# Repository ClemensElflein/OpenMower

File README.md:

<p align="center">
  <a>
    <h1 align="center">OpenMower - The DIY Smart Mowing Robot for Everyone</h1>
    
  </a>
</p>
<br>
<p align="center">
  
</p>
<br>
<p align="center"><b>Join the Discord server for OpenMower discussion:</b></p>
<p align="center"></p>
<br>
<br>

> [!WARNING]
> <p align="center"><b>DISCLAIMER:</b></p>
>
> **IF YOU ARE NOT 100% SURE WHAT YOU ARE DOING, PLEASE DON'T TRY THIS AT HOME! ASK IN [DISCORD](https://discord.gg/jE7QNaSxW7), IF YOU HAVE ANY QUESTIONS!**

> [!IMPORTANT]
> ### New users: start here → [openmower.de](https://openmower.de)
>
> This repository is the central entry point for the OpenMower project. The actual code, firmware and hardware designs live in dedicated repositories — see the [Ecosystem](#ecosystem) section below.

<br>

# About the Project

If you want to see a quick overview, check out this video:

<p align="center">
  
</p>

Let's be honest: The current generation of robotic lawn mowers sucks. Basically all of these bots drive in a random direction until they hit the border of the lawn, rotate for a randomized duration and repeat. **We can do better.**

OpenMower started by disassembling the cheapest off-the-shelf robotic mower we could find (YardForce Classic 500) and replacing its brain with custom hardware and open-source software — turning a dumb random-walk robot into a GPS-guided, map-aware, app-controlled mowing machine.

## Project Goals

:heavy_check_mark: **Autonomous Lawn Mowing:** The device mows the lawn automatically.

:heavy_check_mark: **Good Safety:** Emergency stop if lifted or crashed.

:heavy_check_mark: **No Perimeter Wire Needed:** Flexible support for multiple mowing areas.

:heavy_check_mark: **Low Cost:** Cheaper than a mid-range off-the-shelf product.

:heavy_check_mark: **Open:** Share knowledge and enable others to build their own OpenMower.

:heavy_check_mark: **Nice to Look At:** You should not be ashamed to have an OpenMower mowing your lawn.

:heavy_check_mark: **Avoid Obstacles:** Detect and avoid obstacles during mowing.

:heavy_check_mark: **Rain Detection:** Detect bad weather and pause until conditions improve.

<br>

# Open Mower App

<br>

# Getting Started

**Full documentation and step-by-step build guide:** [openmower.de](https://openmower.de)

The docs cover everything: compatibility checks, hardware shopping list (~€700 excl. mower and RTK base station), robot modification, software setup, and recording your mowing areas.

Before buying anything, read the [System Architecture overview](https://openmower.de/latest/docs/system-architecture/) and the [Step by Step Guide](https://openmower.de/latest/docs/step-by-step-guide/). The build requires intermediate electronics, Linux, and mechanical skills and typically takes a weekend for a YardForce-class mower.

**Need help?** Join the [Discord](https://discord.gg/jE7QNaSxW7) — 2000+ members, active community.

<br>

# Ecosystem

OpenMower is split across purpose-specific repositories, included here as submodules. Clone everything at once:

```bash
git clone --recursive https://github.com/ClemensElflein/OpenMower
```

Or fetch submodules after an existing clone:

```bash
git submodule update --init --recursive
```

## Software

| Repository | Local path | Description |
|---|---|---|
| [ClemensElflein/open_mower_ros](https://github.com/ClemensElflein/open_mower_ros) | `software/open_mower_ros` | ROS navigation, planning and state machine |
| [xtech/openmower-app](https://github.com/xtech/openmower-app) | `software/openmower-app` | Mobile and web app |
| [ClemensElflein/OpenMowerOS](https://github.com/ClemensElflein/OpenMowerOS) | `software/OpenMowerOS` | Operating system image |

## Firmware

| Repository | Local path | Description |
|---|---|---|
| [xtech/fw-openmower-v2](https://github.com/xtech/fw-openmower-v2) | `firmware/fw-openmower-v2` | Mainboard firmware — motor control, sensors, hardware abstraction |
| [ClemensElflein/xesc_firmware](https://github.com/ClemensElflein/xesc_firmware) | `firmware/xesc_firmware` | xESC motor controller firmware |

## Hardware

| Repository | Local path | Description |
|---|---|---|
| [xtech/hw-openmower-universal](https://github.com/xtech/hw-openmower-universal) | `hardware/hw-openmower-universal` | Universal mainboard |
| [xtech/hw-openmower-yardforce](https://github.com/xtech/hw-openmower-yardforce) | `hardware/hw-openmower-yardforce` | YardForce-specific mainboard |
| [xtech/hw-openmower-sabo](https://github.com/xtech/hw-openmower-sabo) | `hardware/hw-openmower-sabo` | Sabo / John Deere mainboard |

<br>

# Compatible Robotic Mowers

Many robotic mowers share the same underlying hardware manufactured by SUMEC Hardware, sold under brands like YardForce, Herkules, and others. By upgrading one of these robots, a large number of devices become OpenMower-capable.

Check the [openmower website](https://openmower.de/latest/docs/getting-started/#is-your-mower-compatible) to check, if your mower is compatible.

<br>

# How You Can Help

- **Build one** — validates the concept and generates useful documentation for others
- **Star ⭐ and watch 👀** this repository — helps with visibility
- **Contribute** — see [CONTRIBUTING.md](./CONTRIBUTING.md)
- **Support** — subscribe to the [YouTube channel](https://youtube.com/c/ClemensElflein)

<br>

# Patents, Local Laws, Liability

Before building a robot based on the designs published here, make sure you are allowed to do so in your specific region. There may be patents and/or laws prohibiting it.

The code/schematics/PCB files are distributed in the hope that they will be useful, but **WITHOUT ANY WARRANTY**; without even the implied warranty of MERCHANTABILITY or FITNESS FOR A PARTICULAR PURPOSE.

This is a documentation of a personal project, shared freely. I am not liable for any damages your devices cause to anyone or anything. You will need real technical know-how to use this project.

# License

**Licenses differ across the project.** Software repositories (ROS, app, OS, firmware) are generally licensed under GPL or MIT — check the `LICENSE` file in each individual repository before use.

This repository documentation is licensed under:

<br /><a rel="license" href="http://creativecommons.org/licenses/by-nc-sa/4.0/">Creative Commons Attribution-NonCommercial-ShareAlike 4.0 International</a>.

Feel free to use the design in private/educational projects. Don't sell the design or products based on it without consent. The goal is to share knowledge, not to enable others to sell this work.

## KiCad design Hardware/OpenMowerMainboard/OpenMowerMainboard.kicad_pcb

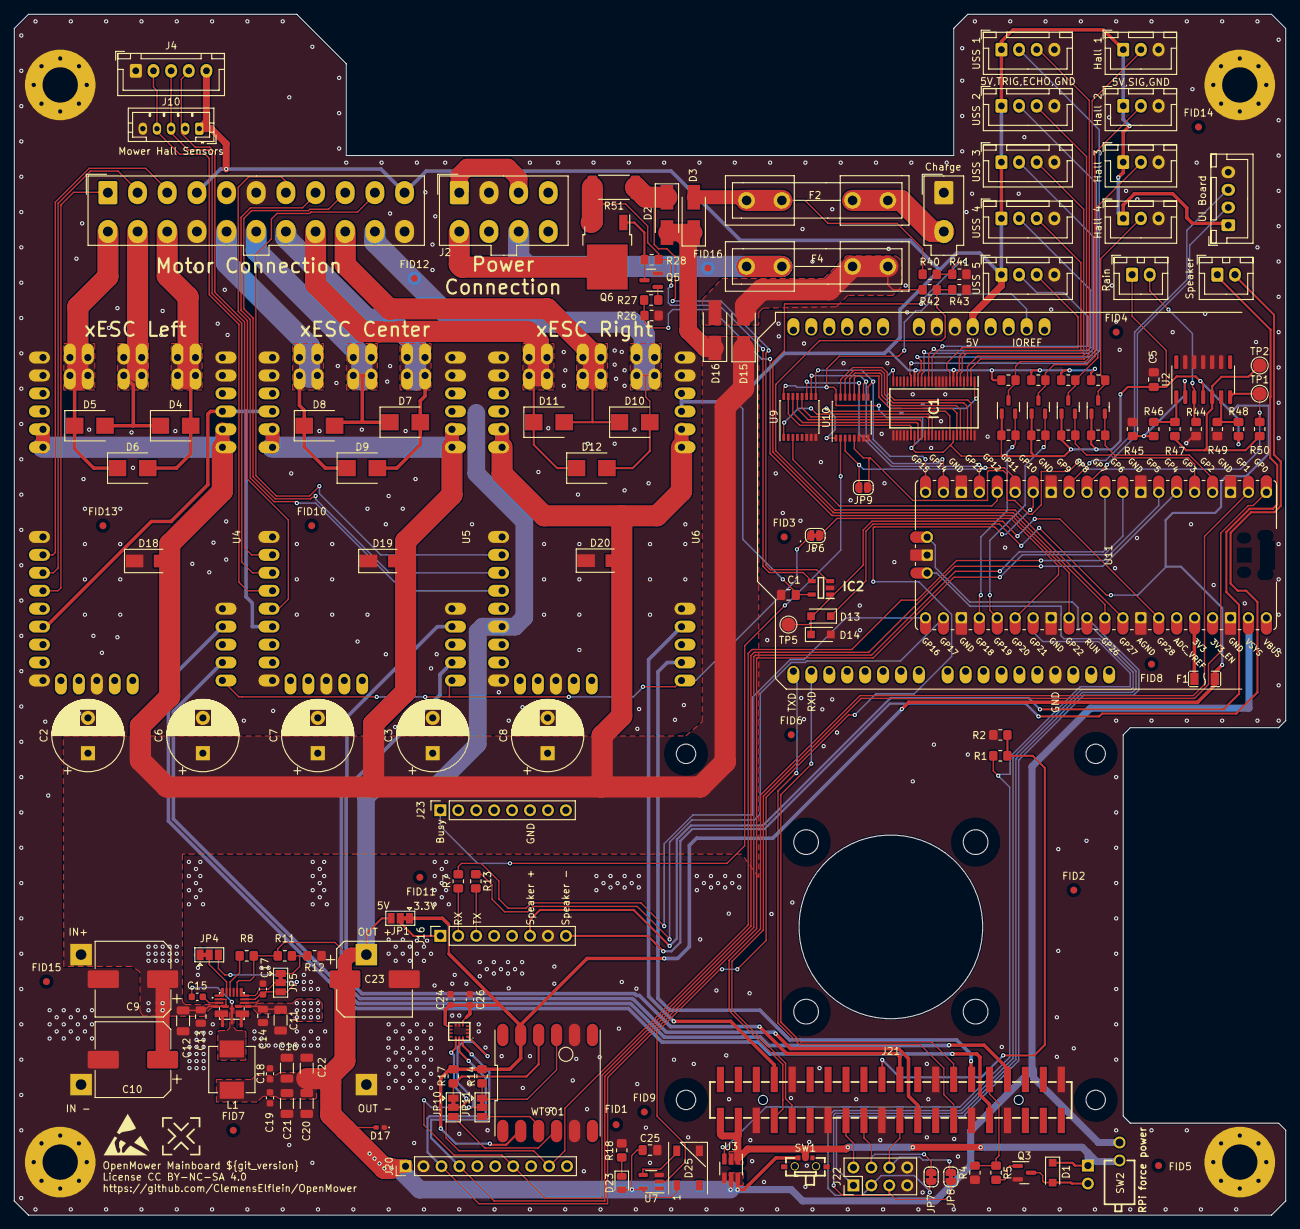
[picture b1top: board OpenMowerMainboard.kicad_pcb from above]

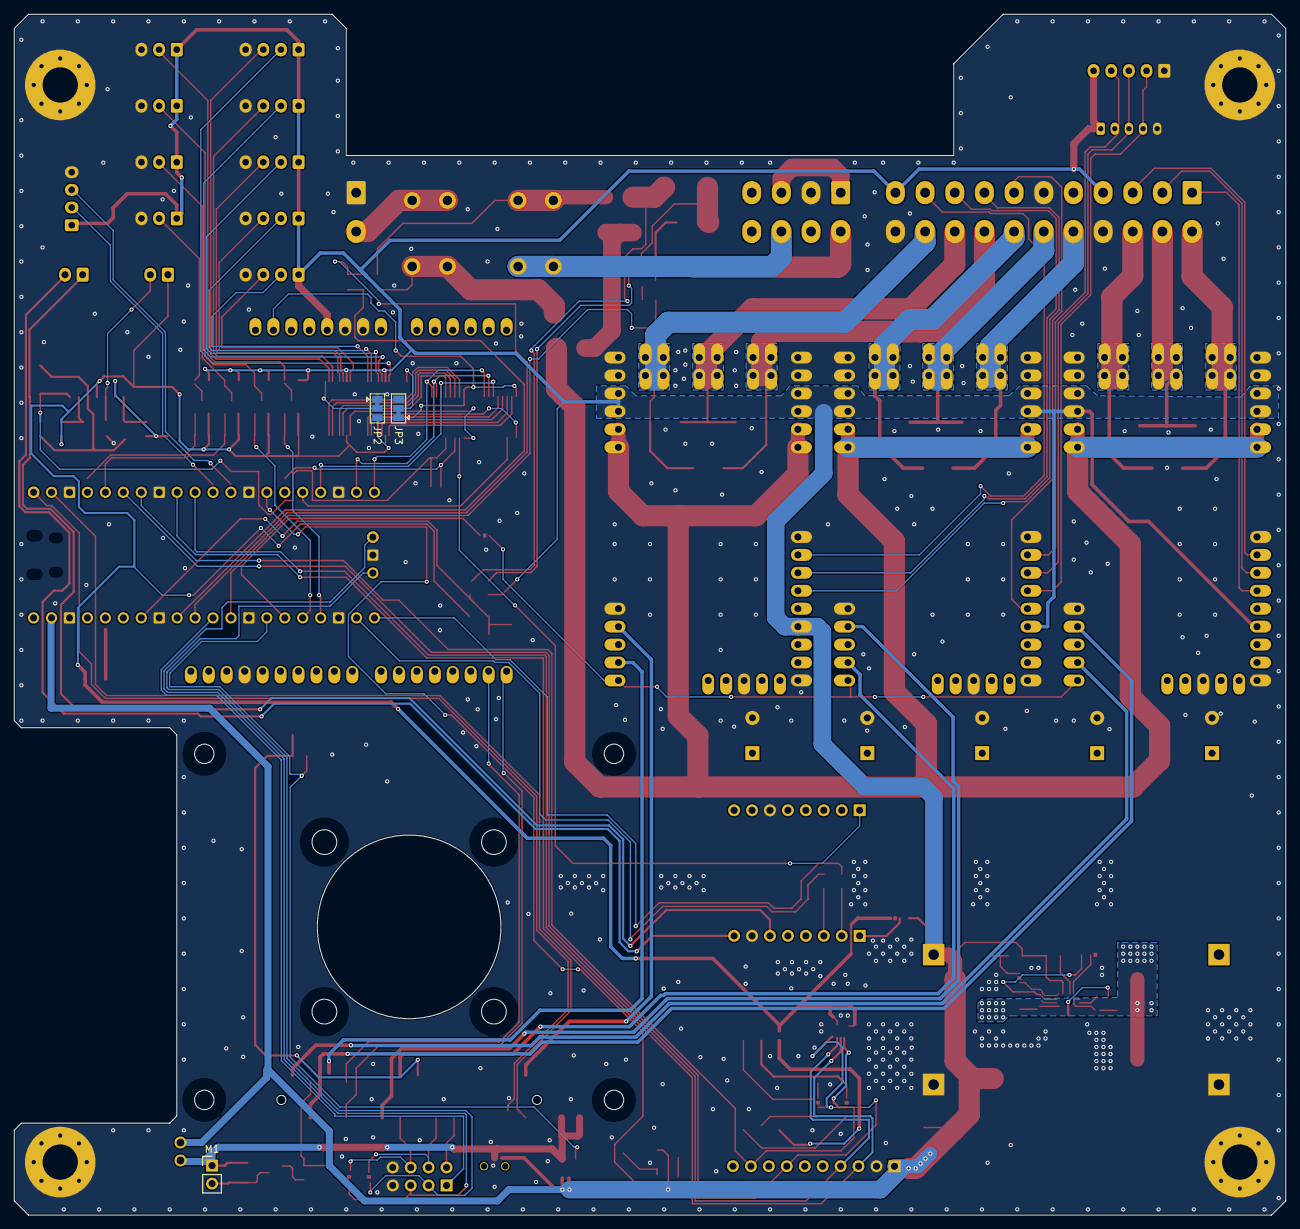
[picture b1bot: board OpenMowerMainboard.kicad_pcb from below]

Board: 2 copper layers, 180.0 x 170.0 mm, 178 parts (3 on the bottom side), 132 nets.

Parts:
AC1201: LSM6DSOTR; LGA-14_2.5X3X0.86_
C1, C5, C25: 100nF; C_0805_2012Metric_Pad1.18x1.45mm_HandSolder
C2, C3, C6, C7, C8: 220uF; CP_Radial_D10.0mm_P5.00mm
C9, C23: 680uF; CP_Elec_10x12.5
C10: DNP; CP_Elec_10x12.5
C11, C12: 4.7uF; C_1206_3216Metric
C13, C14: 1uF; C_0805_2012Metric
C15, C18, C19, C24, C26: 0.1uF; C_0603_1608Metric
C16, C20, C21, C22: 22uF; C_1206_3216Metric
C17: 2.2uF; C_0603_1608Metric
D1: D_Schottky; D_SOD-123F
D2, D3, D15, D16: D_Schottky; D_SMA_Handsoldering
D4, D5, D6, D7, D8, D9, D10, D11, D12: DNP; D_SMB
D13, D14: DNP; D_SOD-123F
D17: DNP; D_0402_1005Metric_Pad0.77x0.64mm_HandSolder
D18, D19, D20: DNP; D_SMA
D23: LED; LED_0805_2012Metric
D25: WS2812B; LED_WS2812B_PLCC4_5.0x5.0mm_P3.2mm
F1: nSMD035-16V; F1206
F2, F4: Fuse; Fuseholder5x20_horiz_open_inline_Type-I
FID1, FID2, FID3, FID4, FID5, FID6, FID7, FID8, FID9, FID10, FID11, FID12, FID13, FID14, FID15, FID16: Fiducial; Fiducial_1mm_Mask2mm
H1, H2, H3, H4: MountingHole_Pad; MountingHole_5mm_Pad_Via
IC1: 74ALVC164245DGG,11; SOP50P810X120-48N
IC2: TSC101CILT; SOT95P280X145-5N
IC3: MAX20405AFOF_VY+T; MAX2040
J1: Conn_02x11_Top_Bottom; Molex_Mini-Fit_Jr_5566-22A_2x11_P4.20mm_Vertical
J2: Conn_02x04_Top_Bottom; Molex_Mini-Fit_Jr_5566-08A_2x04_P4.20mm_Vertical
J3: Conn_01x02; Molex_Mini-Fit_Jr_5566-02A_2x01_P4.20mm_Vertical
J4: Conn_01x05; JST_XH_B5B-XH-A_1x05_P2.50mm_Vertical
J5, J6, J7, J8, J9, J19: Conn_01x04; JST_XH_B4B-XH-A_1x04_P2.50mm_Vertical
J10: Conn_01x05; JST_PH_B5B-PH-K_1x05_P2.00mm_Vertical
J11, J12, J13, J14: Conn_01x03_Male; JST_XH_B3B-XH-A_1x03_P2.50mm_Vertical
J16, J23: Conn_01x08; PinSocket_1x08_P2.54mm_Vertical
J17, J18: Conn_01x02; JST_XH_B2B-XH-A_1x02_P2.50mm_Vertical
J20: Conn_01x10_Female; PinHeader_1x10_P2.54mm_Vertical
J21: Raspberry_Pi_2_3; HDR-SMD_40P-P2.54-V-F-R2-C20-S8.8-EH
J22: Conn_02x04_Odd_Even; PinHeader_2x04_P2.54mm_Vertical
JP1, JP2, JP3, JP4, JP5: SolderJumper_3_Bridged12; SolderJumper-3_P1.3mm_Bridged12_Pad1.0x1.5mm
JP6, JP7, JP8: SolderJumper_2_Bridged; SolderJumper-2_P1.3mm_Bridged_RoundedPad1.0x1.5mm
JP9: SolderJumper_2_Open; SolderJumper-2_P1.3mm_Open_RoundedPad1.0x1.5mm
JP10, JP11: I2C_OR_TTL; SolderJumper-3_P1.3mm_Bridged12_Pad1.0x1.5mm
L1: 4.7uH 5A; L_Vishay_IHLP-2525
LOGO1: LOGO; ESD-Logo_6.6x6mm_SilkScreen
LOGO2: ESD-Logo_6.6x6mm_SilkScreen
M1: Fan; PinHeader_1x02_P2.54mm_Vertical
MH1, MH2, MH3, MH4, MH5, MH6, MH7, MH8: MountingHole_2.7mm_M2.5
Q3, Q5, Q13, Q14, Q15, Q16: BSS138; SOT-23
Q6: Q_PMOS_GDS; TO-252-2
R1, R2, R4, R12, R26, R28, R40, R42, R48, R50: 10k; R_0805_2012Metric_Pad1.20x1.40mm_HandSolder
R3, R6, R7, R9, R10, R13, R15, R16, R18, R19, R20, R41, R43, R45, R47: 1k; R_0805_2012Metric_Pad1.20x1.40mm_HandSolder
R5, R27: 150; R_0805_2012Metric_Pad1.20x1.40mm_HandSolder
R8: DNP; R_0805_2012Metric_Pad1.20x1.40mm_HandSolder
R11: 53k6 1%; R_0805_2012Metric_Pad1.20x1.40mm_HandSolder
R14, R17, R49: 4k7; R_0805_2012Metric_Pad1.20x1.40mm_HandSolder
R44, R46: 47k; R_0805_2012Metric_Pad1.20x1.40mm_HandSolder
R51: 0.003R; R_2512_6332Metric_Pad1.40x3.35mm_HandSolder
SW1: MK-11C04-G013; SW-SMD_MK-11C04-G013
SW2: DA-01BP; SW-TH_DA-01BP
TP1, TP2, TP5: TestPoint; TestPoint_Pad_D2.0mm
U1: DNP; LM2596S_MODULE
U2: MCP604; SOIC-14_3.9x8.7mm_P1.27mm
U3: SIP32509DT; SOT-23-6_Handsoldering
U4, U5, U6: xESC2
U7: SN74LV1T34DBV; SOT-23-5
U9, U10: 74HC4051; SSOP-16_4.4x5.2mm_P0.65mm
U11: Pico; Raspberry_Pi_Pico_SMT_THT
WT901: Conn_02x06_Female; WT901
XA1: Arduino_Uno_Shield

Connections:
+3V3: AC1201.5 (VDDIO), AC1201.8 (VDD), C5.2, C24.1, C26.1, D13.1 (K), F1.2, IC1.31 (VCC(A)_1), IC1.42 (VCC(A)_2), J17.1, JP1.1 (A), JP2.3 (B), JP3.1 (A), Q13.1 (G), Q14.1 (G), Q15.1 (G), Q16.1 (G), R3.1, R9.1, R14.2, R15.1, R17.2, R19.1, R48.2, U2.4 (V+), U9.16 (VCC), U10.16 (VCC), WT901.a2 (VCC), WT901.b2 (VCC), XA1.IORF (IOREF)
+5V: C1.1, C16.1, C18.1, C19.1, C20.1, C21.1, C22.1, C23.1, C25.1, D17.2 (A2), D23.2 (A), D25.1 (VDD), IC1.7 (VCC(B)_1), IC1.18 (VCC(B)_2), IC2.5 (VCC), IC3.13 (OUT), J1.4, J1.11, J4.5, J5.1, J6.1, J7.1, J8.1, J9.1, J10.1, J11.1, J12.1, J13.1, J14.1, J19.1, J20.1, JP1.3 (B), L1.2, R6.1, R8.2, R10.1, R11.2, R16.1, R20.1, SW1.1, SW2.2, U1.3 (OUT+), U3.5 (VIN), U3.6 (VIN), U4.5V, U5.5V, U6.5V, U7.5 (VCC), U11.39 (VSYS), XA1.5V1 (5V)
/CHARGE_CURRENT: D13.2 (A), D14.1 (K), IC2.1 (OUT), TP5.1, U11.34 (GPIO28_ADC2)
/ESCs/ESC_SHUTDOWN: JP6.1 (A), U11.26 (GPIO20)
/ESCs/MC_HALL_U: J4.2, J10.4, U5.4 (HALL_U)
/ESCs/MC_HALL_V: J4.3, J10.3, U5.5 (HALL_V)
/ESCs/MC_HALL_W: J4.4, J10.2, U5.6 (HALL_W)
/ESCs/MC_PHASE_U: D7.2 (A2), D9.2 (A2), J1.18, U5.U
/ESCs/MC_PHASE_V: D7.1 (A1), D8.2 (A2), J1.17, U5.V
/ESCs/MC_PHASE_W: D8.1 (A1), D9.1 (A1), J1.16, U5.W
/ESCs/MC_RX: J21.24 (~CE0/GPIO8), U5.14 (NCS/RX)
/ESCs/MC_TEMP: J1.7, U5.3 (TEMPERATURE)
/ESCs/MC_TX: J21.21 (MISO0/GPIO9), U5.12 (MOSI/TX)
/ESCs/ML_HALL_U: J1.1, U4.4 (HALL_U)
/ESCs/ML_HALL_V: J1.2, U4.5 (HALL_V)
/ESCs/ML_HALL_W: J1.3, U4.6 (HALL_W)
/ESCs/ML_PHASE_U: D4.2 (A2), D6.2 (A2), J1.14, U4.U
/ESCs/ML_PHASE_V: D4.1 (A1), D5.2 (A2), J1.13, U4.V
/ESCs/ML_PHASE_W: D5.1 (A1), D6.1 (A1), J1.12, U4.W
/ESCs/ML_RX: J21.32 (PWM0/GPIO12), U4.14 (NCS/RX)
/ESCs/ML_TX: J21.33 (PWM1/GPIO13), U4.12 (MOSI/TX)
/ESCs/MR_HALL_U: J1.8, U6.4 (HALL_U)
/ESCs/MR_HALL_V: J1.9, U6.5 (HALL_V)
/ESCs/MR_HALL_W: J1.10, U6.6 (HALL_W)
/ESCs/MR_PHASE_U: D10.2 (A2), D12.2 (A2), J1.21, U6.U
/ESCs/MR_PHASE_V: D10.1 (A1), D11.2 (A2), J1.20, U6.V
/ESCs/MR_PHASE_W: D11.1 (A1), D12.1 (A1), J1.19, U6.W
/ESCs/MR_RX: J21.7 (GCLK0/GPIO4), U6.14 (NCS/RX)
/ESCs/MR_TX: J21.29 (GCLK1/GPIO5), U6.12 (MOSI/TX)
/GPS/RXD: J21.27 (ID_SD/GPIO0), XA1.D1 (D1_TX0)
/GPS/TXD: J21.28 (ID_SC/GPIO1), XA1.D0 (D0_RX0)
/IMU/MISO: AC1201.1 (SDO/SA0), J20.7, JP11.2 (C), U11.6 (GPIO4)
/IMU/MOSI: AC1201.14 (SDA), J20.4, U11.10 (GPIO7)
/IMU/SCK: AC1201.13 (SCL), J20.3, U11.9 (GPIO6)
/IMU/~CS: AC1201.12 (CS), J20.9, JP10.2 (C), U11.7 (GPIO5)
/RAIN_DETECTED: JP9.1 (A), R50.2, TP1.1, U2.7, U10.5 (A5)
/RaspberryPi/PICO_RESET: J22.1, U11.30 (RUN)
/RaspberryPi/PICO_SWCLK: J22.5, JP8.1 (A), U11.41 (SWCLK)
/RaspberryPi/PICO_SWDIO: J22.3, JP7.1 (A), U11.43 (SWDIO)
/RaspberryPi/POWER_EN: R1.1, U3.3 (ENABLE), U11.27 (GPIO21)
/RaspberryPi/RASPI_FAN_ON: J21.31 (GCLK2/GPIO6), R4.2, R5.1
/RaspberryPi/RASPI_POWER: D1.1 (K), J21.2 (5V), J21.4 (5V), M1.1 (+), SW1.C, SW2.1, U3.1 (VOUT), U3.2 (VOUT)
/RaspberryPi/UART0_RXD: J21.10 (GPIO15/RXD), U11.1 (GPIO0)
/RaspberryPi/UART0_TXD: J21.8 (GPIO14/TXD), U11.2 (GPIO1)
/RobotConnectors/CHARGE_SHUNT_MINUS: IC2.4 (VM), Q6.3 (S), R28.1, R51.2
/RobotConnectors/CHARGE_SHUNT_PLUS: D2.1 (K), IC2.3 (VP), R51.1
/RobotConnectors/ENABLE_CHARGE: R26.1, R27.1, U11.29 (GPIO22)
/RobotConnectors/HALL_SWITCH_1: Q13.2 (S), R3.2, U11.24 (GPIO18)
/RobotConnectors/HALL_SWITCH_1_5V: J11.2, Q13.3 (D), R6.2
/RobotConnectors/HALL_SWITCH_2: Q14.2 (S), R9.2, U11.25 (GPIO19)
/RobotConnectors/HALL_SWITCH_2_5V: J12.2, Q14.3 (D), R10.2
/RobotConnectors/HALL_SWITCH_3: Q15.2 (S), R15.2, U11.5 (GPIO3)
/RobotConnectors/HALL_SWITCH_3_5V: J13.2, Q15.3 (D), R16.2
/RobotConnectors/HALL_SWITCH_4: Q16.2 (S), R19.2, U11.4 (GPIO2)
/RobotConnectors/HALL_SWITCH_4_5V: J14.2, Q16.3 (D), R20.2
/RobotConnectors/LED_RX: J19.2, U11.11 (GPIO8)
/RobotConnectors/LED_TX: J19.3, U11.12 (GPIO9)
/RobotConnectors/MosfetSwitch/VOUT: J2.5, Q6.2 (D)
/RobotConnectors/RAIN-: J17.2, R44.2, U2.3 (+)
/RobotConnectors/SPEAKER_MINUS: J16.8, J18.2
/RobotConnectors/SPEAKER_PLUS: J16.6, J18.1
/RobotConnectors/USS_1_ECHO: IC1.47 (1A0), U10.15 (A2)
/RobotConnectors/USS_1_ECHO_5V: IC1.2 (1B0), J5.3
/RobotConnectors/USS_1_TRIGGER: IC1.30 (2A4), U9.15 (A2)
/RobotConnectors/USS_1_TRIGGER_5V: IC1.19 (2B4), J5.2
/RobotConnectors/USS_2_ECHO: IC1.46 (1A1), U10.14 (A1)
/RobotConnectors/USS_2_ECHO_5V: IC1.3 (1B1), J6.3
/RobotConnectors/USS_2_TRIGGER: IC1.32 (2A3), U9.14 (A1)
/RobotConnectors/USS_2_TRIGGER_5V: IC1.17 (2B3), J6.2
/RobotConnectors/USS_3_ECHO: IC1.44 (1A2), U10.13 (A0)
/RobotConnectors/USS_3_ECHO_5V: IC1.5 (1B2), J7.3
/RobotConnectors/USS_3_TRIGGER: IC1.33 (2A2), U9.13 (A0)
/RobotConnectors/USS_3_TRIGGER_5V: IC1.16 (2B2), J7.2
/RobotConnectors/USS_4_ECHO: IC1.43 (1A3), U10.12 (A3)
/RobotConnectors/USS_4_ECHO_5V: IC1.6 (1B3), J8.3
/RobotConnectors/USS_4_TRIGGER: IC1.35 (2A1), U9.12 (A3)
/RobotConnectors/USS_4_TRIGGER_5V: IC1.14 (2B1), J8.2
/RobotConnectors/USS_5_ECHO: IC1.41 (1A4), U10.1 (A4)
/RobotConnectors/USS_5_ECHO_5V: IC1.8 (1B4), J9.3
/RobotConnectors/USS_5_TRIGGER: IC1.36 (2A0), U9.1 (A4)
/RobotConnectors/USS_5_TRIGGER_5V: IC1.13 (2B0), J9.2
/RobotConnectors/V_BATTERY: D15.2 (A), D16.2 (A), F4.2, R42.2
/RobotConnectors/V_CHARGE: D3.2 (A), F2.1, R40.2
/pico/MUX_ADDRESS_0: U9.11 (S0), U10.11 (S0), U11.17 (GPIO13)
/pico/MUX_ADDRESS_1: U9.10 (S1), U10.10 (S1), U11.19 (GPIO14)
/pico/MUX_ADDRESS_2: U9.9 (S2), U10.9 (S2), U11.20 (GPIO15)
/pico/MUX_INPUT: JP9.2 (B), U10.3 (A), U11.15 (GPIO11)
/pico/MUX_OUTPUT: U9.3 (A), U11.16 (GPIO12)
/pico/SOUND_BUSY: J23.1, U10.2 (A6)
/pico/SOUND_RX: R13.1, U11.22 (GPIO17)
/pico/SOUND_TX: R7.2, U11.21 (GPIO16)
/pico/V_CHARGE: R40.1, R41.2, U11.31 (GPIO26_ADC0)
/pico/V_IN: R42.1, R43.2, U11.32 (GPIO27_ADC1)
GND: AC1201.2 (SDX), AC1201.3 (SCX), AC1201.6 (GND_1), AC1201.7 (GND_2), C1.2, C2.2, C3.2, C5.1, C6.2, C7.2, C8.2, C9.2, C10.2, C11.2, C12.2, C13.2, C14.2, C16.2, C17.2, C18.2, C19.2, C20.2, C21.2, C22.2, C23.2, C24.2, C25.2, C26.2, D14.2 (A), D17.1 (A1), D18.1 (A1), D19.1 (A1), D20.1 (A1), D25.3 (VSS), H1.1, H2.1, H3.1, H4.1, IC1.4 (GND_1), IC1.9 (1B5), IC1.10 (GND_2), IC1.11 (1B6), IC1.12 (1B7), IC1.15 (GND_3), IC1.21 (GND_4), IC1.25 (~2OE), IC1.26 (2A7), IC1.27 (2A6), IC1.28 (GND_5), IC1.29 (2A5), IC1.34 (GND_6), IC1.39 (GND_7), IC1.45 (GND_8), IC1.48 (~1OE), IC2.2 (GND), IC3.4 (PGND_1), IC3.5 (PGND_2), IC3.7 (PGND_3), IC3.8 (PGND_4), IC3.10 (GND), J1.6, J1.15, J1.22, J2.2, J3.1, J4.1, J5.4, J6.4, J7.4, J8.4, J9.4, J10.5, J11.3, J12.3, J13.3, J14.3, J16.7, J19.4, J20.2, J21.6 (GND), J21.9 (GND), J21.14 (GND), J21.20 (GND), J21.25 (GND), J21.30 (GND), J21.34 (GND), J21.39 (GND), J22.7, J22.8, J23.6, JP2.1 (A), JP3.3 (B), JP4.1 (A), Q3.2 (S), Q5.2 (S), R2.1, R4.1, R12.1, R18.1, R26.2, R41.1, R43.1, R44.1, R45.1, R49.2, U1.1 (IN-), U1.4 (OUT-), U2.9 (-), U2.10 (+), U2.11 (V-), U2.12 (+), U2.13 (-), U3.4 (GND), U4.GND, U5.GND, U6.GND, U7.3 (GND), U9.6 (~E), U9.7 (VEE), U9.8 (GND), U10.6 (~E), U10.7 (VEE), U10.8 (GND), U11.3 (GND), U11.8 (GND), U11.13 (GND), U11.18 (GND), U11.23 (GND), U11.28 (GND), U11.33 (AGND), U11.38 (GND), U11.42 (SWGND), WT901.a5 (GND), WT901.b5 (GND), XA1.GND1 (GND), XA1.GND2 (GND), XA1.GND3 (GND)
unnamed: D1.2 (A), M1.2 (-), Q3.3 (D)
unnamed: D23.1 (K), R18.2
unnamed: D25.4 (DIN), U7.4 (Y)
unnamed: IC1.1 (1DIR), JP2.2 (C)
unnamed: IC1.24 (2DIR), JP3.2 (C)
unnamed: C17.1, IC3.11 (BIAS), JP4.3 (B), JP5.3 (B)
unnamed: C15.1, IC3.2 (BST)
unnamed: IC3.12 (FB_1), IC3.20 (FB_2), JP5.2 (C)
unnamed: C15.2, IC3.6 (LX_1), IC3.19 (LX_2), L1.1
unnamed: IC3.15 (PGOOD), R8.1
unnamed: IC3.16 (SYNC), JP4.2 (C)
unnamed: IC3.17 (SYNCOUT_1), IC3.18 (SYNCOUT_2)
unnamed: J2.1, J2.3
unnamed: F4.1, J2.7
unnamed: F2.2, J3.2
unnamed: J16.1, JP1.2 (C)
unnamed: J16.2, R7.1
unnamed: J16.3, R13.2
unnamed: J21.16 (GPIO23), J22.2
unnamed: J21.18 (GPIO24), J22.4, JP7.2 (B)
unnamed: J21.22 (GPIO25), J22.6, JP8.2 (B)
unnamed: J21.19 (MOSI0/GPIO10), R1.2, R2.2
unnamed: JP5.1 (A), R11.1, R12.2
unnamed: JP6.2 (B), U4.11 (MISO), U5.11 (MISO), U6.11 (MISO)
unnamed: JP10.1 (A), R17.1, WT901.b3 (SCL)
unnamed: JP10.3 (B), WT901.a4 (TX)
unnamed: JP11.1 (A), R14.1, WT901.b4 (SDA)
unnamed: JP11.3 (B), WT901.a3 (RX)
unnamed: Q3.1 (G), R5.2
unnamed: Q5.3 (D), Q6.1 (G), R28.2
unnamed: Q5.1 (G), R27.2
unnamed: R46.1, R47.1, U2.1
unnamed: R45.2, R46.2, U2.2 (-)
unnamed: R47.2, R50.1, TP2.1, U2.5 (+)
unnamed: R48.1, R49.1, U2.6 (-)
unnamed: F1.1, U11.36 (3V3)
unnamed: U7.2 (A), U11.14 (GPIO10)
V_BATT: C2.1, C3.1, C6.1, C7.1, C8.1, C9.1, C10.1, C11.1, C12.1, C13.1, C14.1, D2.2 (A), D3.1 (K), D15.1 (K), D16.1 (K), D18.2 (A2), D19.2 (A2), D20.2 (A2), IC3.1 (EN), IC3.3 (SUP_1), IC3.9 (SUP_2), U1.2 (IN+), U4.VM (VIN), U5.VM (VIN), U6.VM (VIN)

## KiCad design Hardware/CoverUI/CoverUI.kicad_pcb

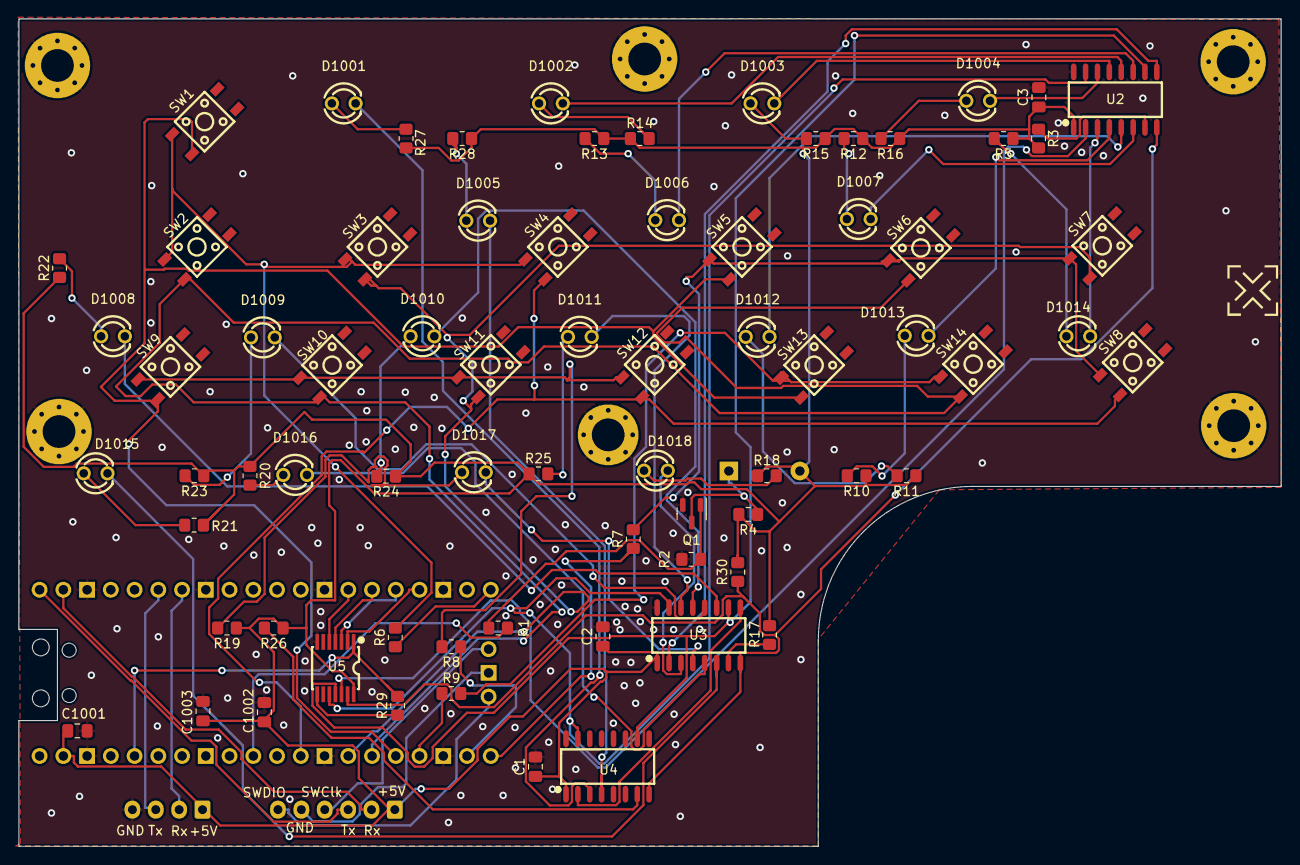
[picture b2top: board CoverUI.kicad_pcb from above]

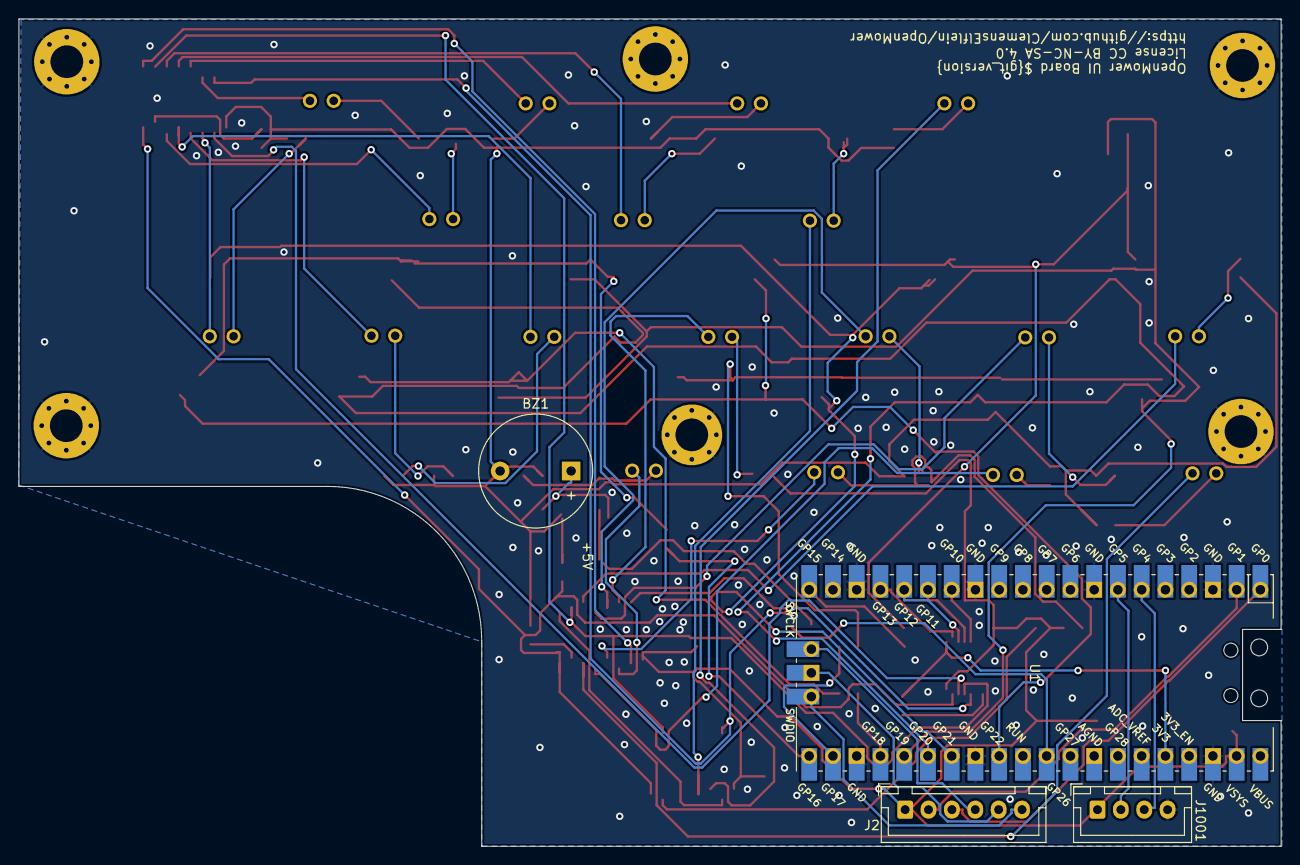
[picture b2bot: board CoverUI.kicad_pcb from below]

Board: 2 copper layers, 135.0 x 88.5 mm, 102 parts (4 on the bottom side), 75 nets.

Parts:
BZ1: Buzzer; Buzzer_12x9.5RM7.6
C1, C2, C3, C1001, C1002: 100nF; C_0805_2012Metric_Pad1.18x1.45mm_HandSolder
C1003: 1uF; C_0805_2012Metric_Pad1.18x1.45mm_HandSolder
D1001, D1002, D1003, D1004, D1005, D1006, D1007, D1008, D1009, D1010, D1011, D1012, D1013, D1014, D1015, D1016, D1017, D1018: 20mA 2V, Red; LED-TH_BD3.0-P2.54-FD
H1001, H1002, H1003, H1004, H1005, H1006: MountingHole_Pad; MountingHole_3.5mm_Pad_Via
J2: Conn_01x06_Male; JST_XH_B6B-XH-A_1x06_P2.50mm_Vertical
J1001: Conn_01x04_Male; JST_XH_B4B-XH-A_1x04_P2.50mm_Vertical
Q1: BSS138; SOT-23
R1, R4: 1k; R_0805_2012Metric_Pad1.20x1.40mm_HandSolder
R2: 47k; R_0805_2012Metric_Pad1.20x1.40mm_HandSolder
R3, R6, R7, R8, R9, R17, R26, R29, R30: 10k; R_0805_2012Metric_Pad1.20x1.40mm_HandSolder
R5, R10, R11, R12, R13, R14, R15, R16, R18, R19, R20, R21, R22, R23, R24, R25, R27, R28: 150; R_0805_2012Metric_Pad1.20x1.40mm_HandSolder
SP01, SP02, SP03, SP04, SP05, SP06, SP07, SP08, SP09, SP10, SP11, SP12, SP13, SP14, SP15, SP16: LedSpacer; LED_SPACER_3mm
SP17, SP18, SP20: LED_SPACER_3mm
SW1, SW2, SW3, SW4, SW5, SW6, SW7, SW8, SW9, SW10, SW11, SW12, SW13, SW14: SW_MEC_5G; SW-SMD_4P-L4.5-W4.5-P3.00-LS7.0
U1: Raspberry-Pico; RPi_Pico_SMD_TH
U2, U3, U4: TPIC6C596DRG4; SOIC-16_L10.8-W4.5-P1.27-LS6.8-BL
U5: RS0104YQ; TSSOP-14_L5.0-W4.4-P0.65-LS6.4-BL

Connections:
+3.3V: R29.2, U1.36 (3V3), U5.1 (VCCA)
+5V: BZ1.2 (+), C1.1, C2.1, C3.1, C1001.1, C1002.1, C1003.1, J2.1, J1001.1, R3.1, R4.2, R5.1, R10.1, R11.1, R12.1, R13.1, R14.1, R15.1, R16.1, R17.1, R18.1, R19.1, R20.1, R21.1, R22.1, R23.1, R24.1, R25.1, R26.1, R27.1, R28.1, R30.2, U1.39 (VSYS), U2.1 (VCC), U3.1 (VCC), U4.1 (VCC), U5.14 (VCCB)
/LEDmux/G: R30.1, U2.8 (~G), U3.8 (~G), U4.8 (~G), U5.13 (B1)
/LEDmux/G_3.3V: U1.17 (GPIO13), U5.2 (A1)
/LEDmux/RCK: U2.10 (RCK), U3.10 (RCK), U4.10 (RCK), U5.11 (B3)
/LEDmux/RCK_3.3V: U1.15 (GPIO11), U5.4 (A3)
/LEDmux/SER: U2.2 (SER/IN), U5.12 (B2)
/LEDmux/SER_3.3V: U1.16 (GPIO12), U5.3 (A2)
/LEDmux/SRCK: U2.15 (SRCK), U3.15 (SRCK), U4.15 (SRCK), U5.10 (B4)
/LEDmux/SRCK_3.3V: U1.14 (GPIO10), U5.5 (A4)
/RaspberryPico/GP15: R6.1, U1.20 (GPIO15)
/RaspberryPico/GP16: R7.1, U1.21 (GPIO16)
/RaspberryPico/GP17: R8.1, U1.22 (GPIO17)
/RaspberryPico/GP18: R9.1, U1.24 (GPIO18)
/RaspberryPico/GP19: SW1.3 (B), SW5.3 (B), SW9.3 (B), SW13.3 (B), U1.25 (GPIO19)
/RaspberryPico/GP20: SW2.3 (B), SW6.3 (B), SW10.3 (B), SW14.3 (B), U1.26 (GPIO20)
/RaspberryPico/GP21: SW3.3 (B), SW7.3 (B), SW11.3 (B), U1.27 (GPIO21)
/RaspberryPico/GP22: SW4.3 (B), SW8.3 (B), SW12.3 (B), U1.29 (GPIO22)
/RaspberryPico/GP26: R1.1, U1.31 (GPIO26_ADC0)
/RaspberryPico/PiCo_RX: J1001.2, U1.7 (GPIO5)
/RaspberryPico/PiCo_TX: J1001.3, U1.6 (GPIO4)
GND: C1.2, C2.2, C3.2, C1001.2, C1002.2, C1003.2, H1001.1, H1002.1, H1003.1, H1004.1, H1005.1, H1006.1, J1001.4, Q1.2 (S), R2.2, U1.3 (GND), U1.8 (GND), U1.13 (GND), U1.18 (GND), U1.23 (GND), U1.28 (GND), U1.38 (GND), U2.16 (GND), U3.16 (GND), U4.16 (GND), U5.7 (GND)
unnamed: BZ1.1 (-), Q1.3 (D), R4.1
unnamed: D1001.1 (A), R27.2
unnamed: D1001.2 (K), U4.3 (DRAIN0)
unnamed: D1002.1 (A), R14.2
unnamed: D1002.2 (K), U2.12 (DRAIN5)
unnamed: D1003.1 (A), R15.2
unnamed: D1003.2 (K), U2.13 (DRAIN6)
unnamed: D1004.1 (A), R16.2
unnamed: D1004.2 (K), U2.14 (DRAIN7)
unnamed: D1005.1 (A), R28.2
unnamed: D1005.2 (K), U4.4 (DRAIN1)
unnamed: D1006.1 (A), R13.2
unnamed: D1006.2 (K), U2.11 (DRAIN4)
unnamed: D1007.1 (A), R12.2
unnamed: D1007.2 (K), U2.6 (DRAIN3)
unnamed: D1008.1 (A), R22.2
unnamed: D1008.2 (K), U3.11 (DRAIN4)
unnamed: D1009.1 (A), R23.2
unnamed: D1009.2 (K), U3.12 (DRAIN5)
unnamed: D1010.1 (A), R24.2
unnamed: D1010.2 (K), U3.13 (DRAIN6)
unnamed: D1011.1 (A), R25.2
unnamed: D1011.2 (K), U3.14 (DRAIN7)
unnamed: D1012.1 (A), R11.2
unnamed: D1012.2 (K), U2.5 (DRAIN2)
unnamed: D1013.1 (A), R10.2
unnamed: D1013.2 (K), U2.4 (DRAIN1)
unnamed: D1014.1 (A), R5.2
unnamed: D1014.2 (K), U2.3 (DRAIN0)
unnamed: D1015.1 (A), R21.2
unnamed: D1015.2 (K), U3.6 (DRAIN3)
unnamed: D1016.1 (A), R20.2
unnamed: D1016.2 (K), U3.5 (DRAIN2)
unnamed: D1017.1 (A), R19.2
unnamed: D1017.2 (K), U3.4 (DRAIN1)
unnamed: D1018.1 (A), R18.2
unnamed: D1018.2 (K), U3.3 (DRAIN0)
unnamed: J2.2, U1.2 (GPIO1)
unnamed: J2.3, U1.1 (GPIO0)
unnamed: J2.4, U1.41 (SWCLK)
unnamed: J2.5, U1.42 (GND)
unnamed: J2.6, U1.43 (SWDIO)
unnamed: Q1.1 (G), R1.2, R2.1
unnamed: R3.2, U2.7 (~CLR)
unnamed: R6.2, SW1.1 (A), SW2.1 (A), SW3.1 (A), SW4.1 (A)
unnamed: R7.2, SW5.1 (A), SW6.1 (A), SW7.1 (A), SW8.1 (A)
unnamed: R8.2, SW9.1 (A), SW10.1 (A), SW11.1 (A), SW12.1 (A)
unnamed: R9.2, SW13.1 (A), SW14.1 (A)
unnamed: R17.2, U3.7 (~CLR)
unnamed: R26.2, U4.7 (~CLR)
unnamed: R29.1, U5.8 (OE)
unnamed: U2.9 (SER/OUT), U3.2 (SER/IN)
unnamed: U3.9 (SER/OUT), U4.2 (SER/IN)

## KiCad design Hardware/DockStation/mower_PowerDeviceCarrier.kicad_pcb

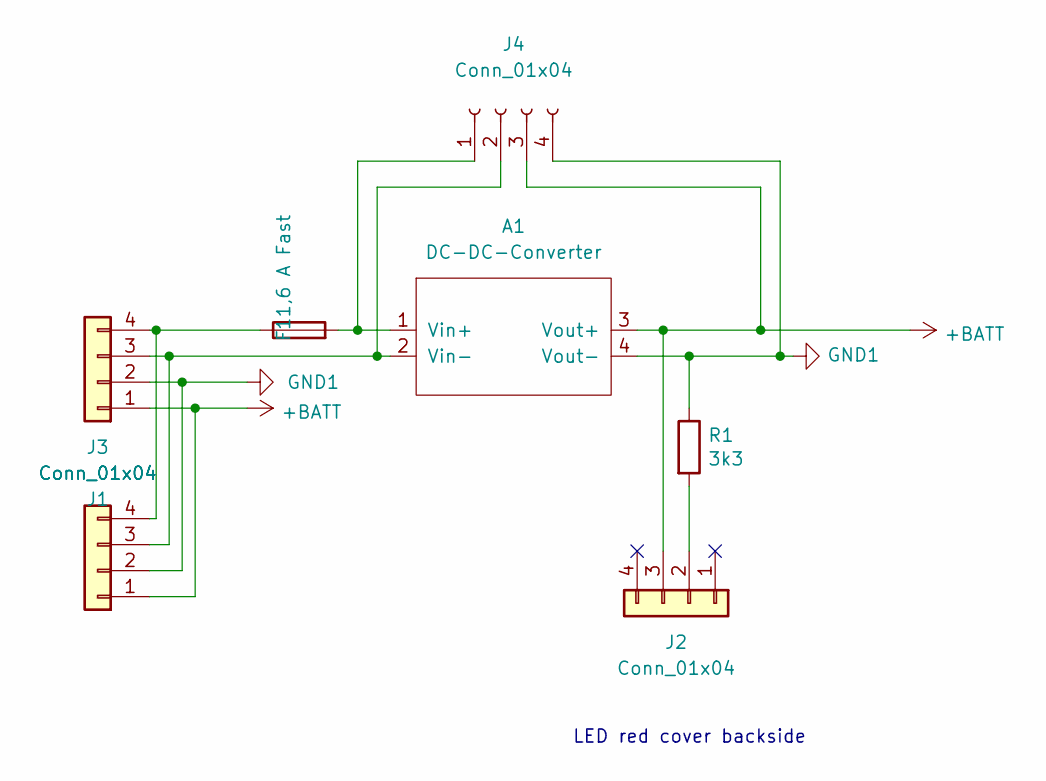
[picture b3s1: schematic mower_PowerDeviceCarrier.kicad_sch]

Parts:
A1: DC-DC-Converter; DC-DC-XL4016
F1: 1,6 A Fast; Fuseholder5x20_horiz_open_inline_Type-I
J1: Conn_01x04; PhoenixContact_MSTBVA_2,5_4-G-5,08_1x04_P5.08mm_Vertical
J2: Conn_01x04; PinHeader_1x04_P2.54mm_Horizontal
J3: Conn_01x04; PhoenixContact_MCV_1,5_4-G-3.81_1x04_P3.81mm_Vertical
J4: Conn_01x04; PinHeader_1x07_P2.54mm_Vertical
R1: 3k3; R_Axial_DIN0414_L11.9mm_D4.5mm_P15.24mm_Horizontal

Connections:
+BATT: A1.3 (Vout+), J1.1, J2.3, J3.1, J4.3
GND1: A1.4 (Vout-), J1.2, J3.2, J4.4, R1.1
unnamed: A1.1 (Vin+), F1.2, J4.1
unnamed: A1.2 (Vin-), J1.3, J3.3, J4.2
unnamed: F1.1, J1.4, J3.4
unnamed: J2.2, R1.2

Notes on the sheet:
LED red cover backside

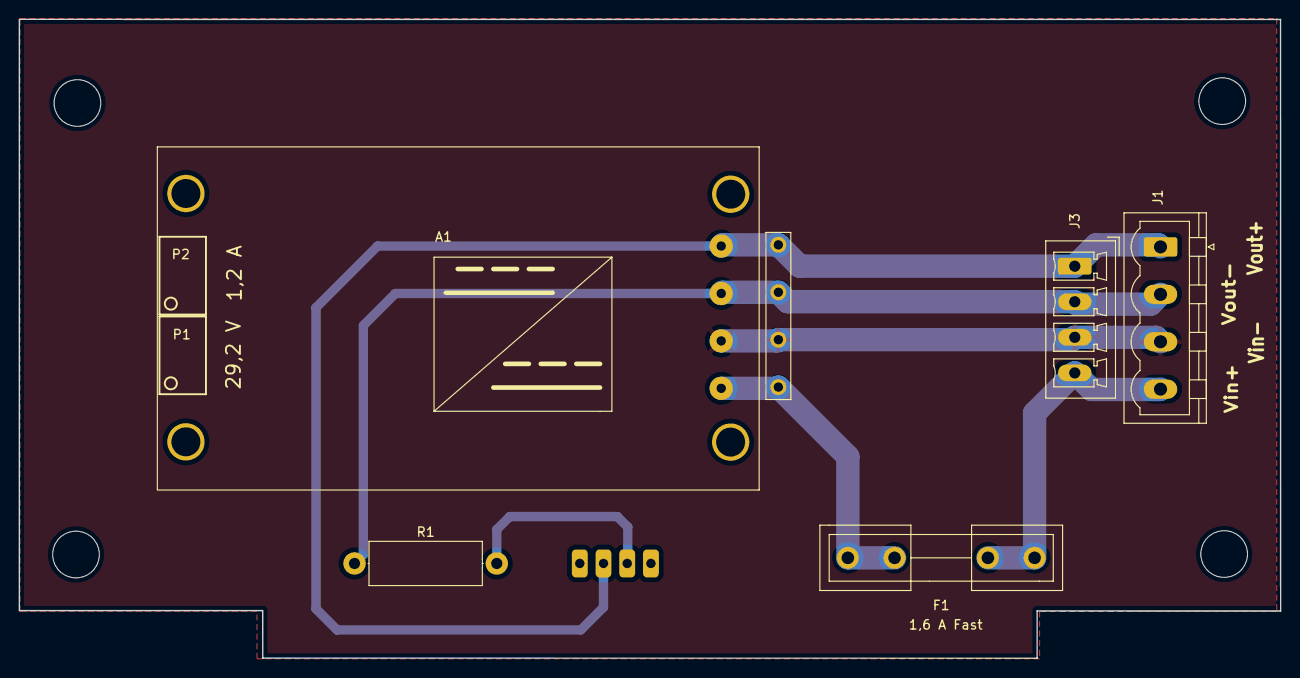
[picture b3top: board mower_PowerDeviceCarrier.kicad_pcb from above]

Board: 2 copper layers, 135.1 x 68.4 mm, 7 parts (1 on the bottom side), 6 nets.

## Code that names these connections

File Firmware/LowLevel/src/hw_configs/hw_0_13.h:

#ifndef HW_0_13_H
#define HW_0_13_H

#include <SPI.h>

/**
 * This HW version uses the following Resources:
 * UART0 - ROS Communication
 * SPI0 / UART1 - IMU
 * PIO Neopixel
 * PIO UART: LED
 * PIO UART: Sound
 */

#define WT901_WIRE Wire

#define PIN_WT901_SDA 8
#define PIN_WT901_SCL 9

#define PIN_IMU_CS 5
#define PIN_IMU_MOSI 7
#define PIN_IMU_MISO 4
#define PIN_IMU_SCK 6

#define PIN_ANALOG_BATTERY_VOLTAGE 27
#define PIN_ANALOG_CHARGE_VOLTAGE 26
#define PIN_ANALOG_CHARGE_CURRENT 28

#define PIN_ENABLE_CHARGE 22

#define PIN_ESC_SHUTDOWN 20
#define PIN_RASPI_POWER 21

#define PIN_EMERGENCY_1 18
#define PIN_EMERGENCY_2 19
#define PIN_EMERGENCY_3 3
#define PIN_EMERGENCY_4 2

#define PIN_MUX_IN 11
#define PIN_MUX_OUT 12
#define PIN_MUX_ADDRESS_0 13
#define PIN_MUX_ADDRESS_1 14
#define PIN_MUX_ADDRESS_2 15

#define PIN_NEOPIXEL 10

#define PIN_UI_TX 8
#define PIN_UI_RX 9

#ifdef ENABLE_SOUND_MODULE
#define PIN_SOUND_TX 16
#define PIN_SOUND_RX 17
#endif



#endif

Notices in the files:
Hardware/CoverUI/CoverUI.kicad_pcb:
License CC BY-NC-SA 4.0
